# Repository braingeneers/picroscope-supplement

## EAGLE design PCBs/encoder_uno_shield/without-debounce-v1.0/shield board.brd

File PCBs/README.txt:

Power distribution board -> V8
Relay hub -> V3R1 -> JLCPCB
Below light -> V6 -> JLCPCB
Overhead light -> R5 -> PCBWAY

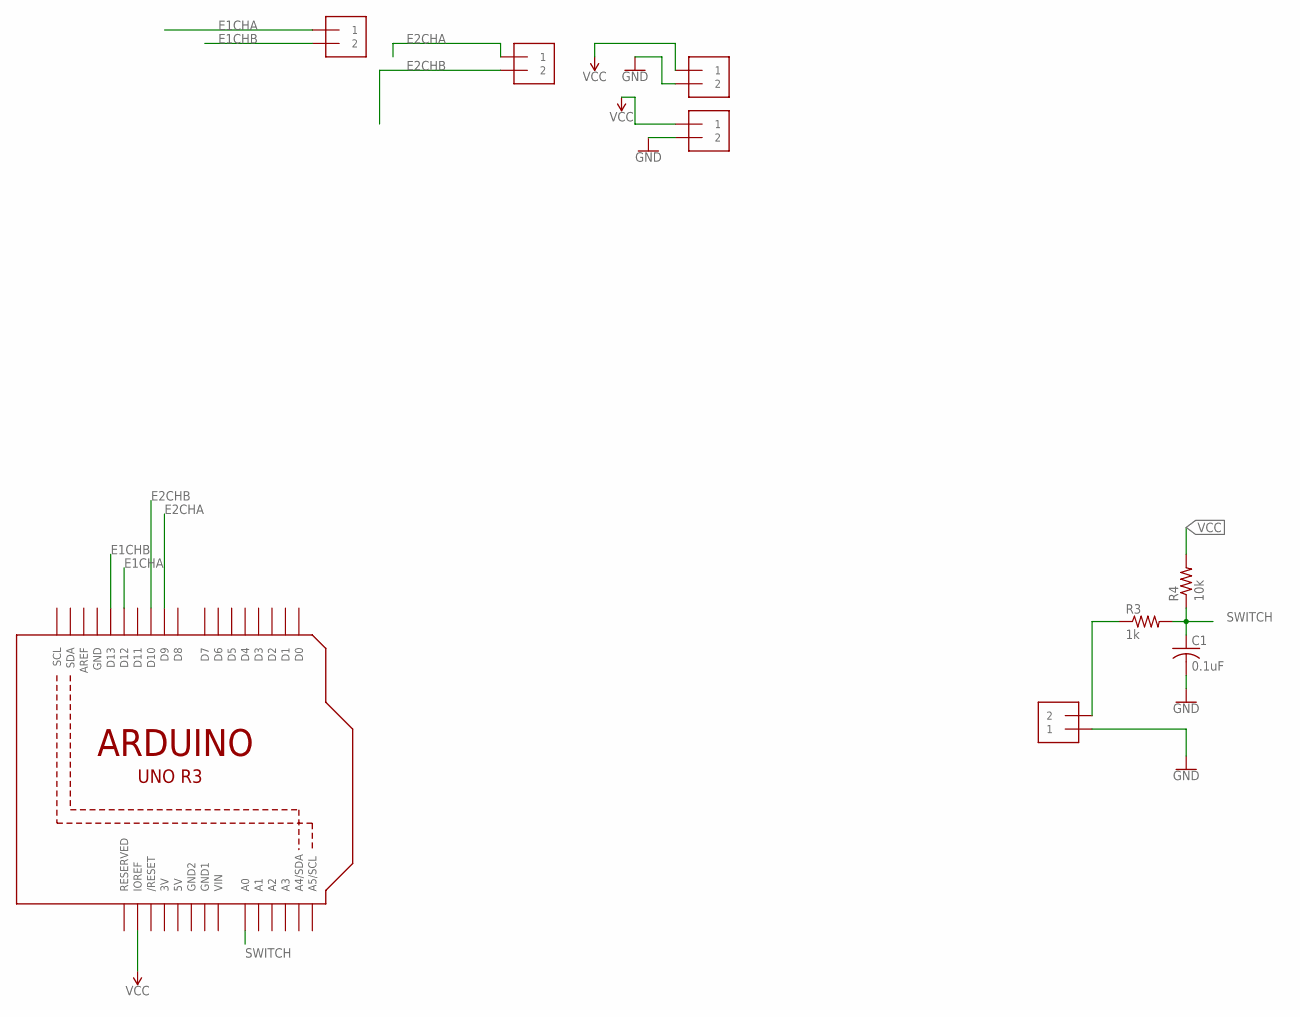
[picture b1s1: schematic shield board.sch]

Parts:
C1: 0.1uF; C0603
R3: 1k; R0603
R4: 10k; R0603
U1: ARDUINOR3-BPLACE
U$2, U$3, U$4, U$5, U$6: MOLEX_0039301022; MINI-FIT_JR_CONN

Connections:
3V: U1.3V
E1CHA: U1.D12, U$5.P$2 (1)
E1CHB: U1.D13, U$5.P$1 (2)
E2CHA: U1.D9, U$6.P$2 (1)
E2CHB: U1.D10, U$6.P$1 (2)
GND: C1.2, U1.GND, U$2.P$2 (1), U$3.P$1 (2), U$4.P$1 (2)
GND1: U1.GND1
GND2: U1.GND2
unnamed: R3.1, U$2.P$1 (2)
SWITCH: C1.1, R3.2, R4.1, U1.A0
VCC: R4.2, U1.5V, U1.IOREF, U$3.P$2 (1), U$4.P$2 (1)
VIN: U1.VIN

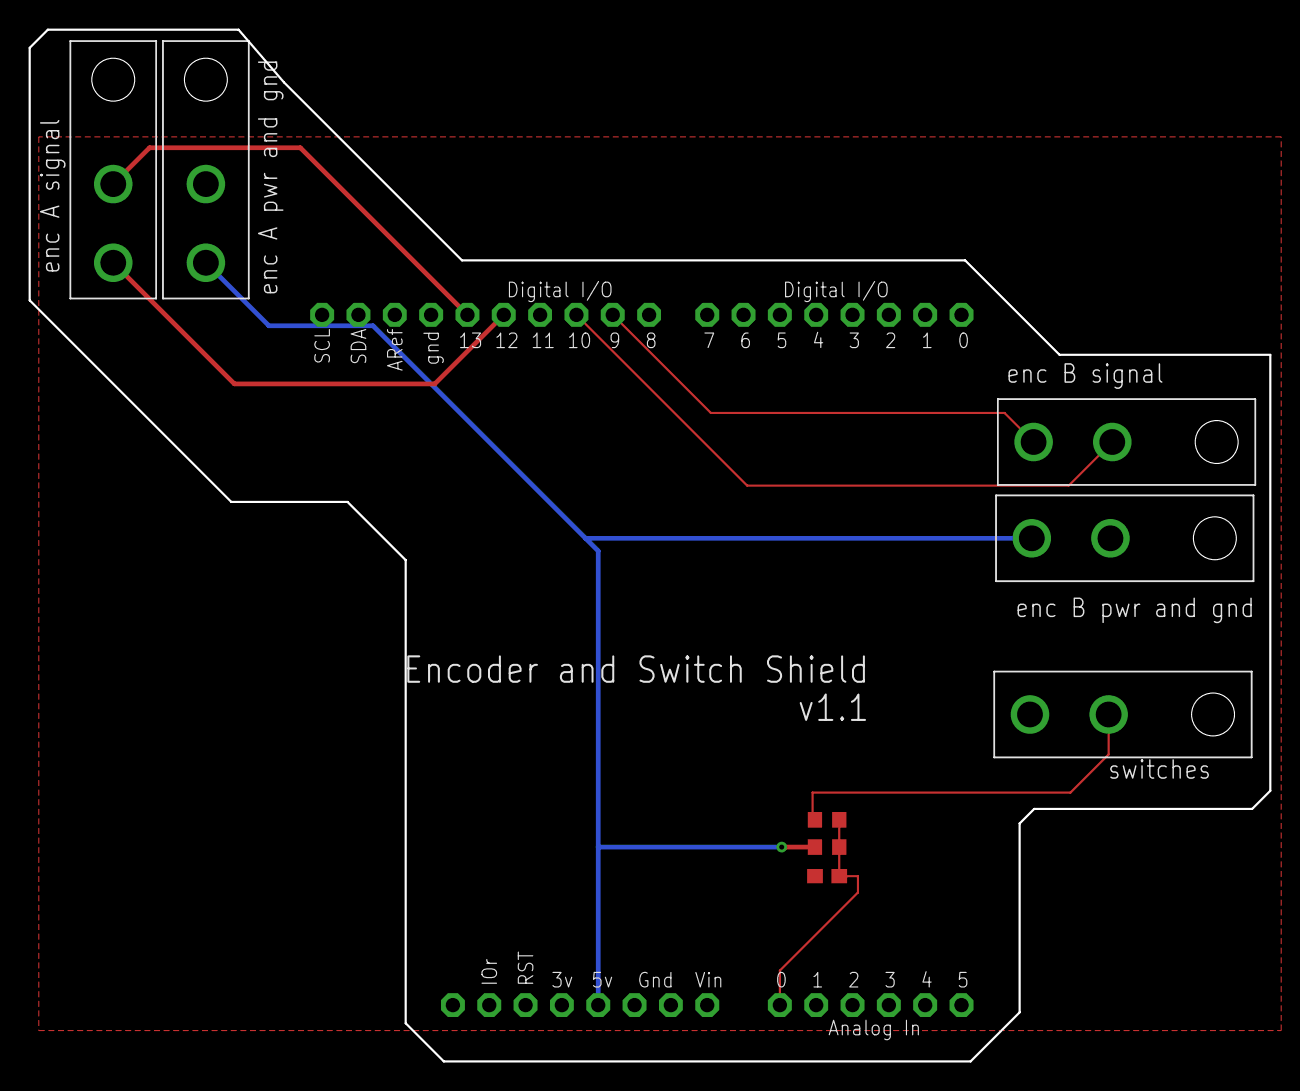
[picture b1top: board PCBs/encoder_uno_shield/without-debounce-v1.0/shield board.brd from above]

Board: 2 copper layers, 86.7 x 72.1 mm, 9 parts (0 on the bottom side), 8 nets.

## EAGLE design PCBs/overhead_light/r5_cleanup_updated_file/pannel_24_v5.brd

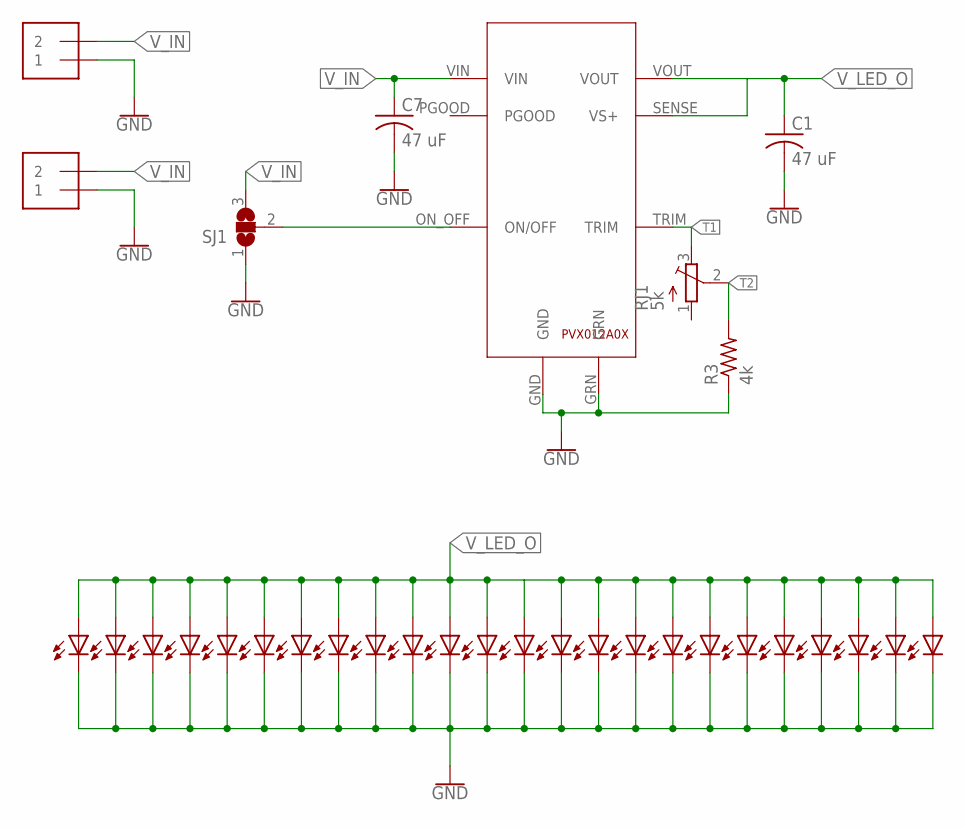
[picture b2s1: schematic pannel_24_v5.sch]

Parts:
C1, C7: 47 uF; C1210
R3: 4k; R0603
RJ1: 5k; 3223W
SJ1: SJ2W; SJ_2
U$1, U$2, U$3, U$4, U$5, U$6, U$7, U$8, U$9, U$10, U$11, U$12, U$13, U$14, U$15, U$16, U$17, U$18, U$19, U$20, U$21, U$22, U$23, U$24: LED; 3WLED
U$25: PVX012A0XV1; PVX012A0X
U$26, U$27: MOLEX_0039301022; MINI-FIT_JR_CONN

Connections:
GND: C1.2, C7.2, R3.1, SJ1.1, U$1.P$2 (C), U$2.P$2 (C), U$3.P$2 (C), U$4.P$2 (C), U$5.P$2 (C), U$6.P$2 (C), U$7.P$2 (C), U$8.P$2 (C), U$9.P$2 (C), U$10.P$2 (C), U$11.P$2 (C), U$12.P$2 (C), U$13.P$2 (C), U$14.P$2 (C), U$15.P$2 (C), U$16.P$2 (C), U$17.P$2 (C), U$18.P$2 (C), U$19.P$2 (C), U$20.P$2 (C), U$21.P$2 (C), U$22.P$2 (C), U$23.P$2 (C), U$24.P$2 (C), U$25.GND, U$25.GRN, U$26.P$2 (1), U$27.P$2 (1)
ON_OFF: SJ1.2, U$25.ON_OFF (ON/OFF)
T1: RJ1.3 (E), U$25.TRIM
T2: R3.2, RJ1.2 (S)
V_IN: C7.1, SJ1.3, U$25.VIN, U$26.P$1 (2), U$27.P$1 (2)
V_LED_O: C1.1, U$1.P$1 (A), U$2.P$1 (A), U$3.P$1 (A), U$4.P$1 (A), U$5.P$1 (A), U$6.P$1 (A), U$7.P$1 (A), U$8.P$1 (A), U$9.P$1 (A), U$10.P$1 (A), U$11.P$1 (A), U$12.P$1 (A), U$13.P$1 (A), U$14.P$1 (A), U$15.P$1 (A), U$16.P$1 (A), U$17.P$1 (A), U$18.P$1 (A), U$19.P$1 (A), U$20.P$1 (A), U$21.P$1 (A), U$22.P$1 (A), U$23.P$1 (A), U$24.P$1 (A), U$25.SENSE (VS+), U$25.VOUT

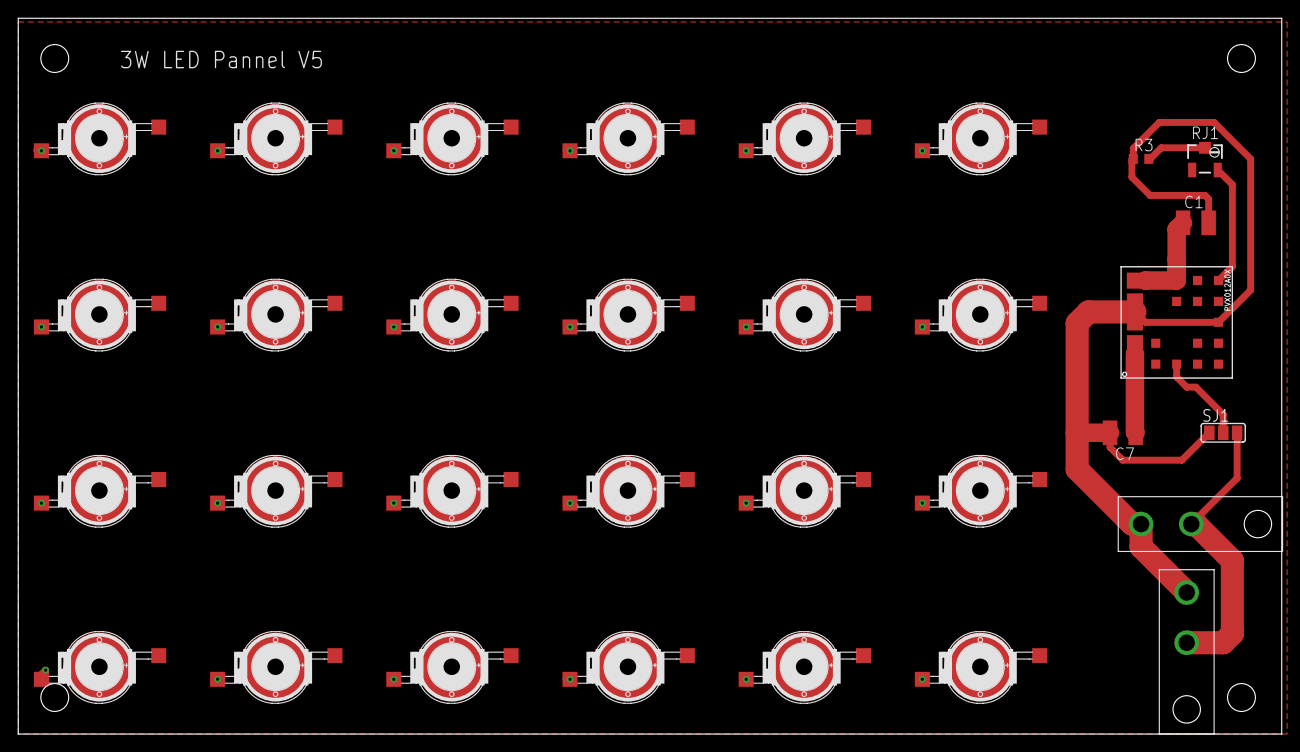
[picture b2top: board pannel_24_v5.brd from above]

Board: 2 copper layers, 138.4 x 78.4 mm, 32 parts (0 on the bottom side), 6 nets.

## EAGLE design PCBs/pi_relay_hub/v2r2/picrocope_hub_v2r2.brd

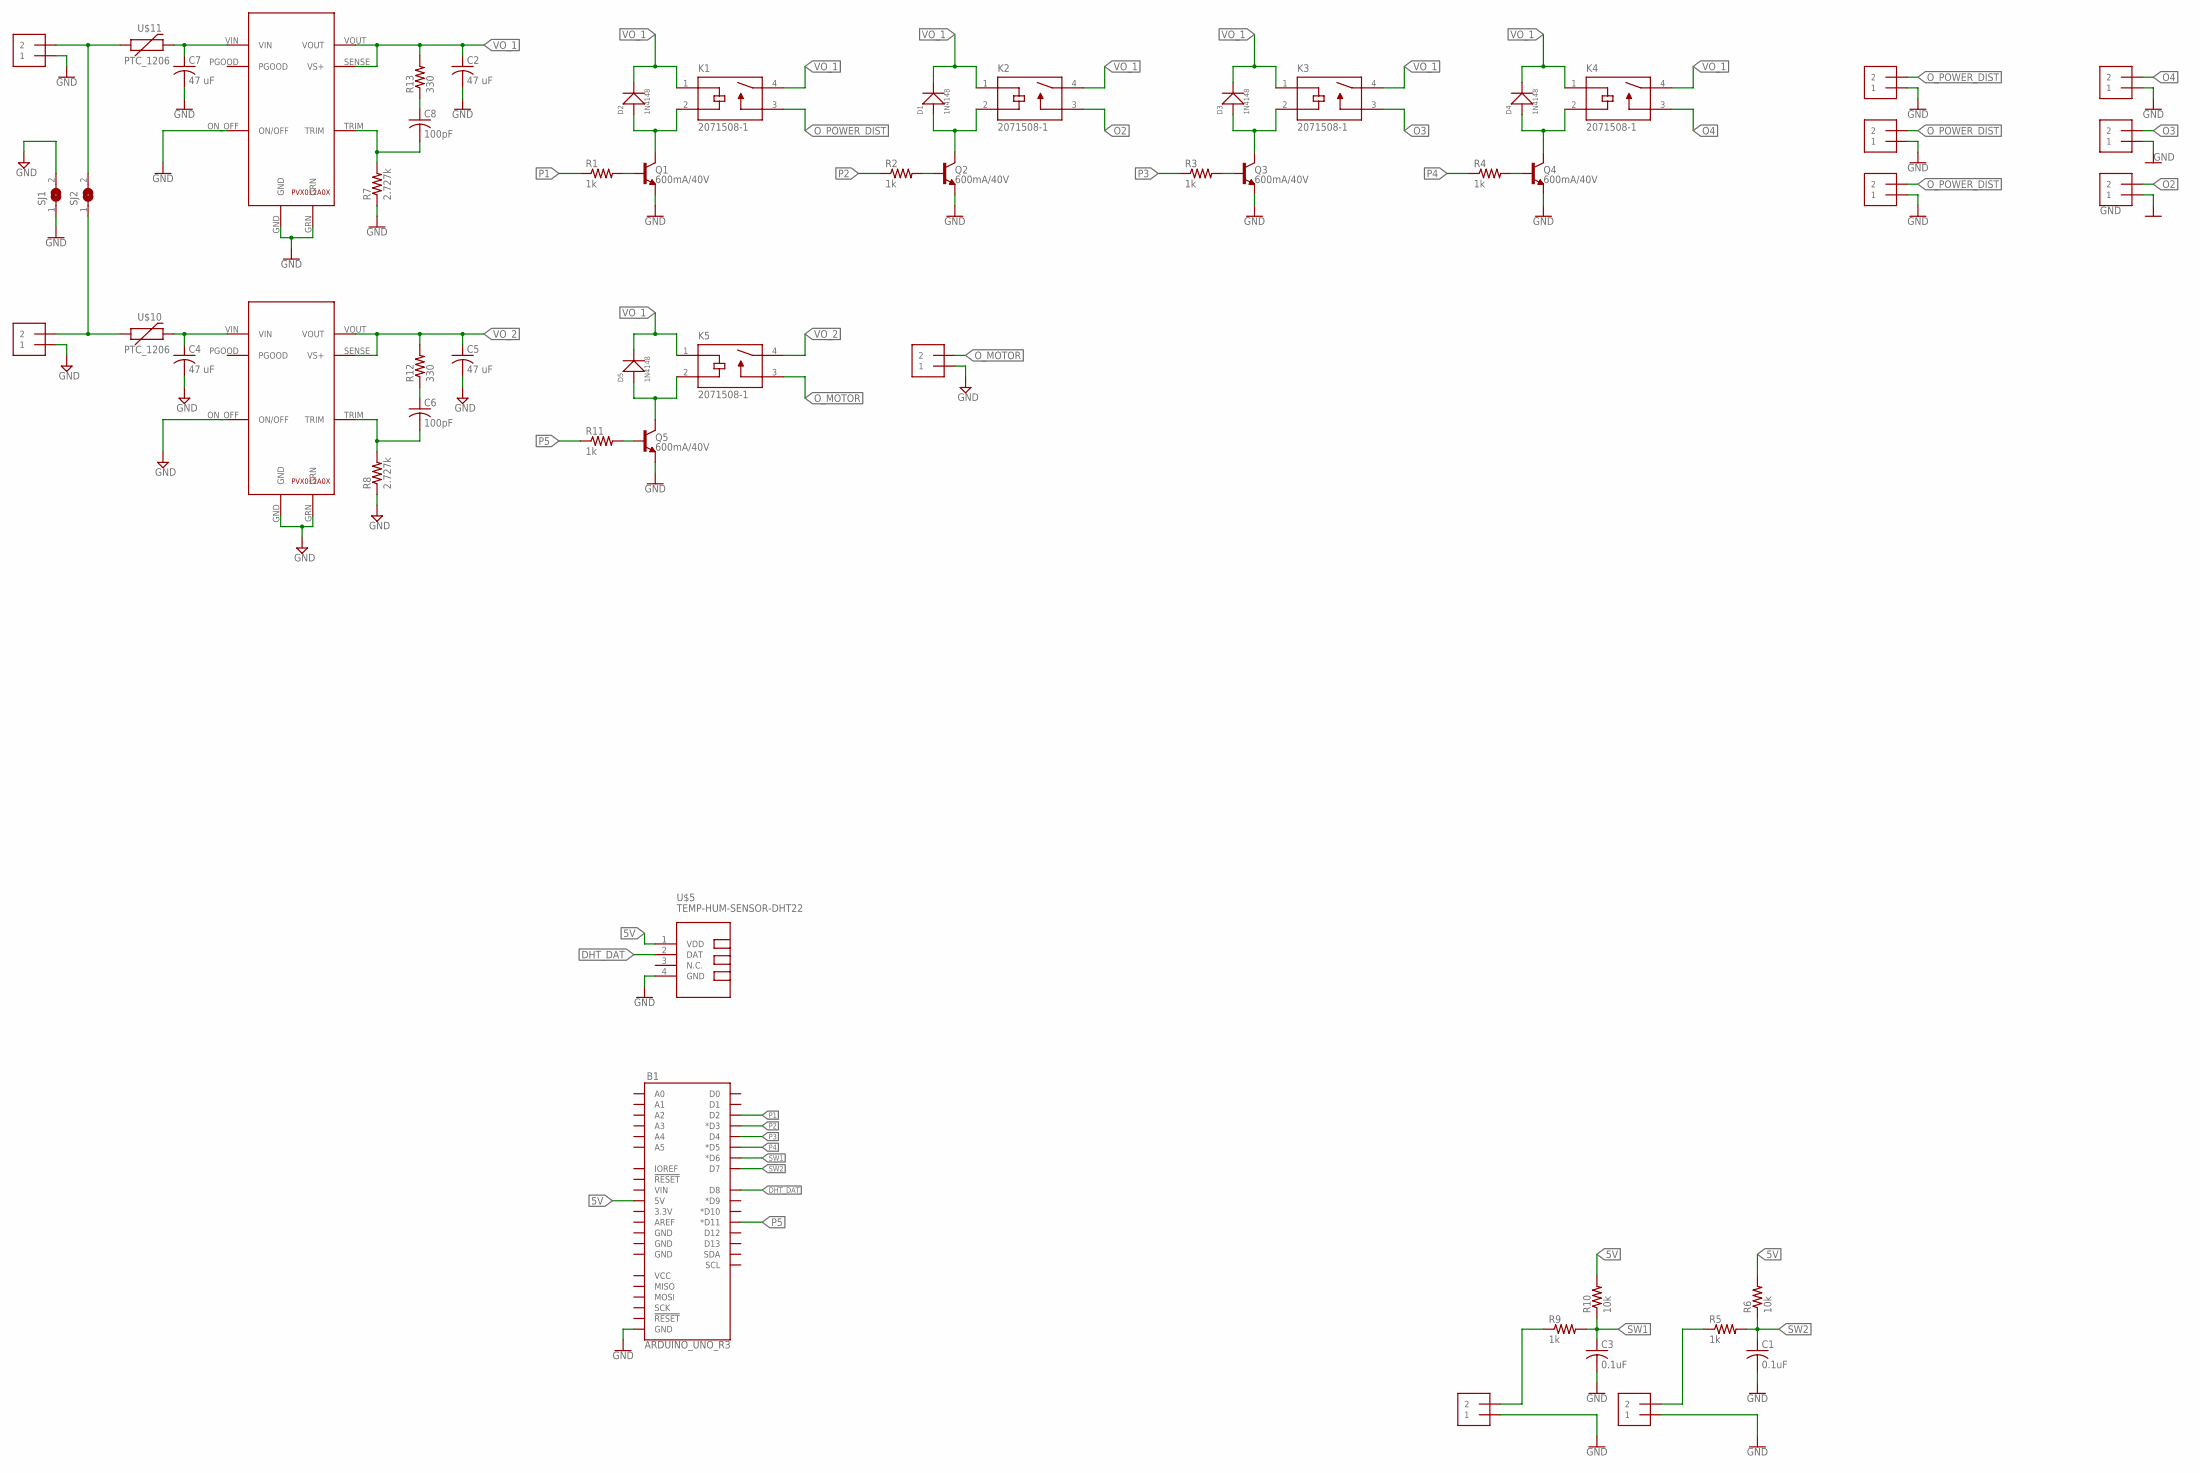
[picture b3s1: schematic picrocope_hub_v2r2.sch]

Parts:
B1: ARDUINO_UNO_R3; ARDUINO_R3
C1, C3: 0.1uF; C0603
C2, C4, C5, C7: 47 uF; C1210
C6, C8: 100pF; C0603
D1, D2, D3, D4, D5: 1N4148; LL-34
K1, K2, K3, K4, K5: 2071508-1; RELAY_2071508-1
Q1, Q2, Q3, Q4, Q5: 600mA/40V; SOT23-3
R1, R2, R3, R4, R5, R9, R11: 1k; R0603
R6, R10: 10k; R0603
R7, R8: 2.727k; R0603
R12, R13: 330; R0603
SJ1, SJ2: SJ
U$1, U$2: PVX012A0XV1; PVX012A0X
U$3, U$4, U$6, U$7, U$8, U$9, U$12, U$13, U$14: MOLEX_0039301022; MINI-FIT_JR_CONN
U$5: TEMP-HUM-SENSOR-DHT22
U$10, U$11: PTC_1206; 1206
U$15, U$16: MOLEX_0039296028; MINI-FIT_JR_VERTICAL_CONN

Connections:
5V: B1.5V, R6.2, R10.2, U$5.1 (VDD)
DHT_DAT: B1.D8, U$5.2 (DAT)
GND: B1.GND@1 (GND), C1.2, C2.2, C3.2, C7.2, Q1.2 (E), Q2.2 (E), Q3.2 (E), Q4.2 (E), Q5.2 (E), R7.1, SJ1.1, U$1.GND, U$1.GRN, U$1.ON_OFF (ON/OFF), U$3.P$2 (1), U$5.4 (GND), U$6.P$2 (1), U$7.P$2 (1), U$8.P$2 (1), U$9.P$2 (1), U$12.P$2 (1), U$13.P$2 (1), U$15.P$1 (1), U$16.P$1 (1)
GND2: C4.2, C5.2, R8.1, SJ1.2, U$2.GND, U$2.GRN, U$2.ON_OFF (ON/OFF), U$4.P$2 (1), U$14.P$2 (1)
unnamed: Q1.1 (B), R1.2
unnamed: D2.A (+), K1.2 (COIL2), Q1.3 (C)
unnamed: SJ2.1, U$4.P$1 (2), U$10.1
unnamed: R5.1, U$16.P$2 (2)
unnamed: Q2.1 (B), R2.2
unnamed: D1.A (+), K2.2 (COIL2), Q2.3 (C)
unnamed: Q3.1 (B), R3.2
unnamed: D3.A (+), K3.2 (COIL2), Q3.3 (C)
unnamed: Q4.1 (B), R4.2
unnamed: D4.A (+), K4.2 (COIL2), Q4.3 (C)
unnamed: R9.1, U$15.P$2 (2)
unnamed: Q5.1 (B), R11.2
unnamed: C6.1, R12.1
unnamed: C8.1, R13.1
unnamed: D5.A (+), K5.2 (COIL2), Q5.3 (C)
unnamed: C6.2, R8.2, U$2.TRIM
unnamed: C8.2, R7.2, U$1.TRIM
unnamed: SJ2.2, U$3.P$1 (2), U$11.1
O2: K2.3 (NO), U$7.P$1 (2)
O3: K3.3 (NO), U$8.P$1 (2)
O4: K4.3 (NO), U$9.P$1 (2)
O_MOTOR: K5.3 (NO), U$14.P$1 (2)
O_POWER_DIST: K1.3 (NO), U$6.P$1 (2), U$12.P$1 (2), U$13.P$1 (2)
P1: B1.D2, R1.1
P2: B1.D3 (*D3), R2.1
P3: B1.D4, R3.1
P4: B1.D5 (*D5), R4.1
P5: B1.D11 (*D11), R11.1
SW1: B1.D6 (*D6), C3.1, R9.2, R10.1
SW2: B1.D7, C1.1, R5.2, R6.1
VIN_1: C7.1, U$1.VIN, U$11.2
VIN_2: C4.1, U$2.VIN, U$10.2
VO_1: C2.1, D1.C (-), D2.C (-), D3.C (-), D4.C (-), D5.C (-), K1.1 (COIL1), K1.4 (COM), K2.1 (COIL1), K2.4 (COM), K3.1 (COIL1), K3.4 (COM), K4.1 (COIL1), K4.4 (COM), K5.1 (COIL1), R13.2, U$1.SENSE (VS+), U$1.VOUT
VO_2: C5.1, K5.4 (COM), R12.2, U$2.SENSE (VS+), U$2.VOUT

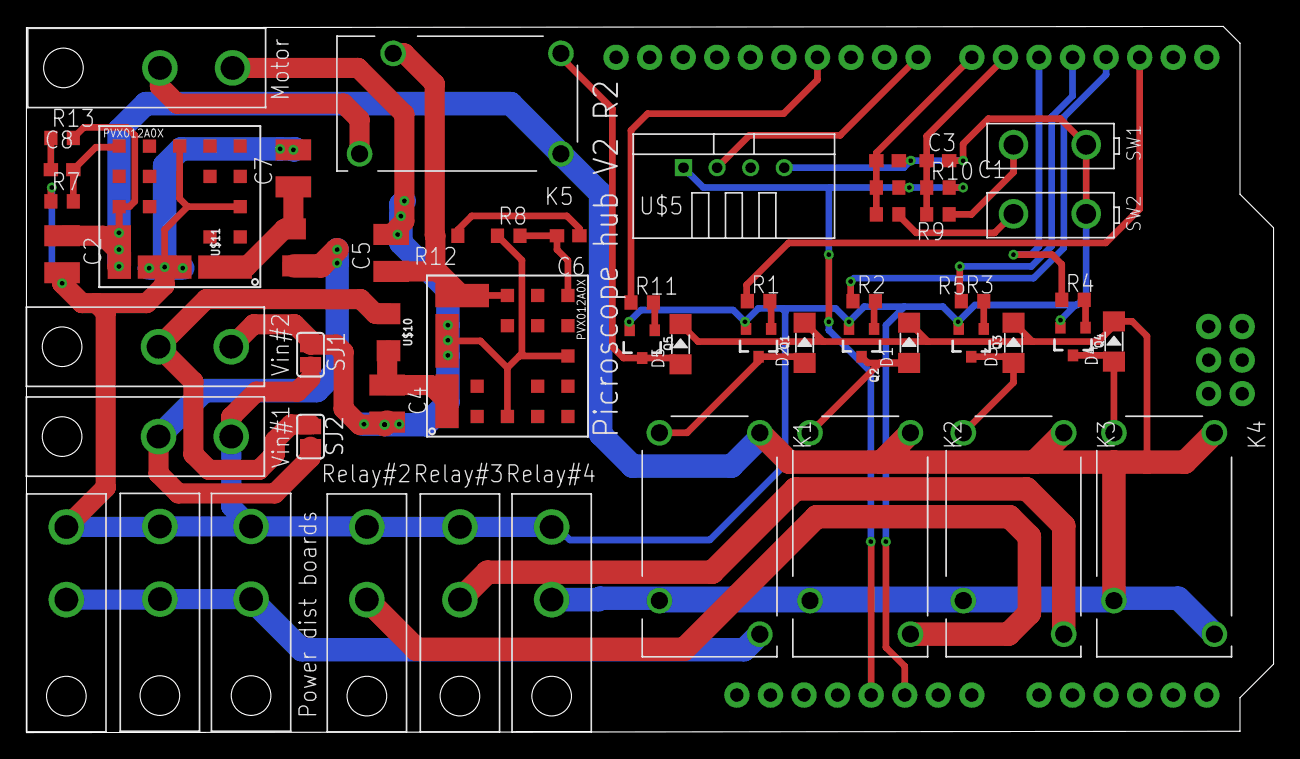
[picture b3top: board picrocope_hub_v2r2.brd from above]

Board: 2 copper layers, 94.4 x 53.4 mm, 55 parts (0 on the bottom side), 38 nets.

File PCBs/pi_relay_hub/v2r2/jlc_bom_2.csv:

Comment,Designator,Footprint,LCSC Part #(optional)
0.1uF,C1,C0603,C14663
47 uF,C2,C1210,C77101
0.1uF,C3,C0603,C14663
47 uF,C4,C1210,C77101
47 uF,C5,C1210,C77101
100pF,C6,C0603,C14858
47 uF,C7,C1210,C77101
100pF,C8,C0603,C14858
1N4148,D1,LL-34,C81598
1N4148,D2,LL-34,C81598
1N4148,D3,LL-34,C81598
1N4148,D4,LL-34,C81598
1N4148,D5,LL-34,C81598
600mA/40V,Q1,SOT23-3,C8512
600mA/40V,Q2,SOT23-3,C8512
600mA/40V,Q3,SOT23-3,C8512
600mA/40V,Q4,SOT23-3,C8512
600mA/40V,Q5,SOT23-3,C8512
1k,R1,R0603,C21190
1k,R2,R0603,C21190
1k,R3,R0603,C21190
1k,R4,R0603,C21190
1k,R5,R0603,C21190
10k,R6,R0603,C25804
2.727k,R7,R0603,C13167
2.727k,R8,R0603,C13167
1k,R9,R0603,C21190
10k,R10,R0603,C25804
1k,R11,R0603,C21190
330,R12,R0603,C23138
330,R13,R0603,C23138

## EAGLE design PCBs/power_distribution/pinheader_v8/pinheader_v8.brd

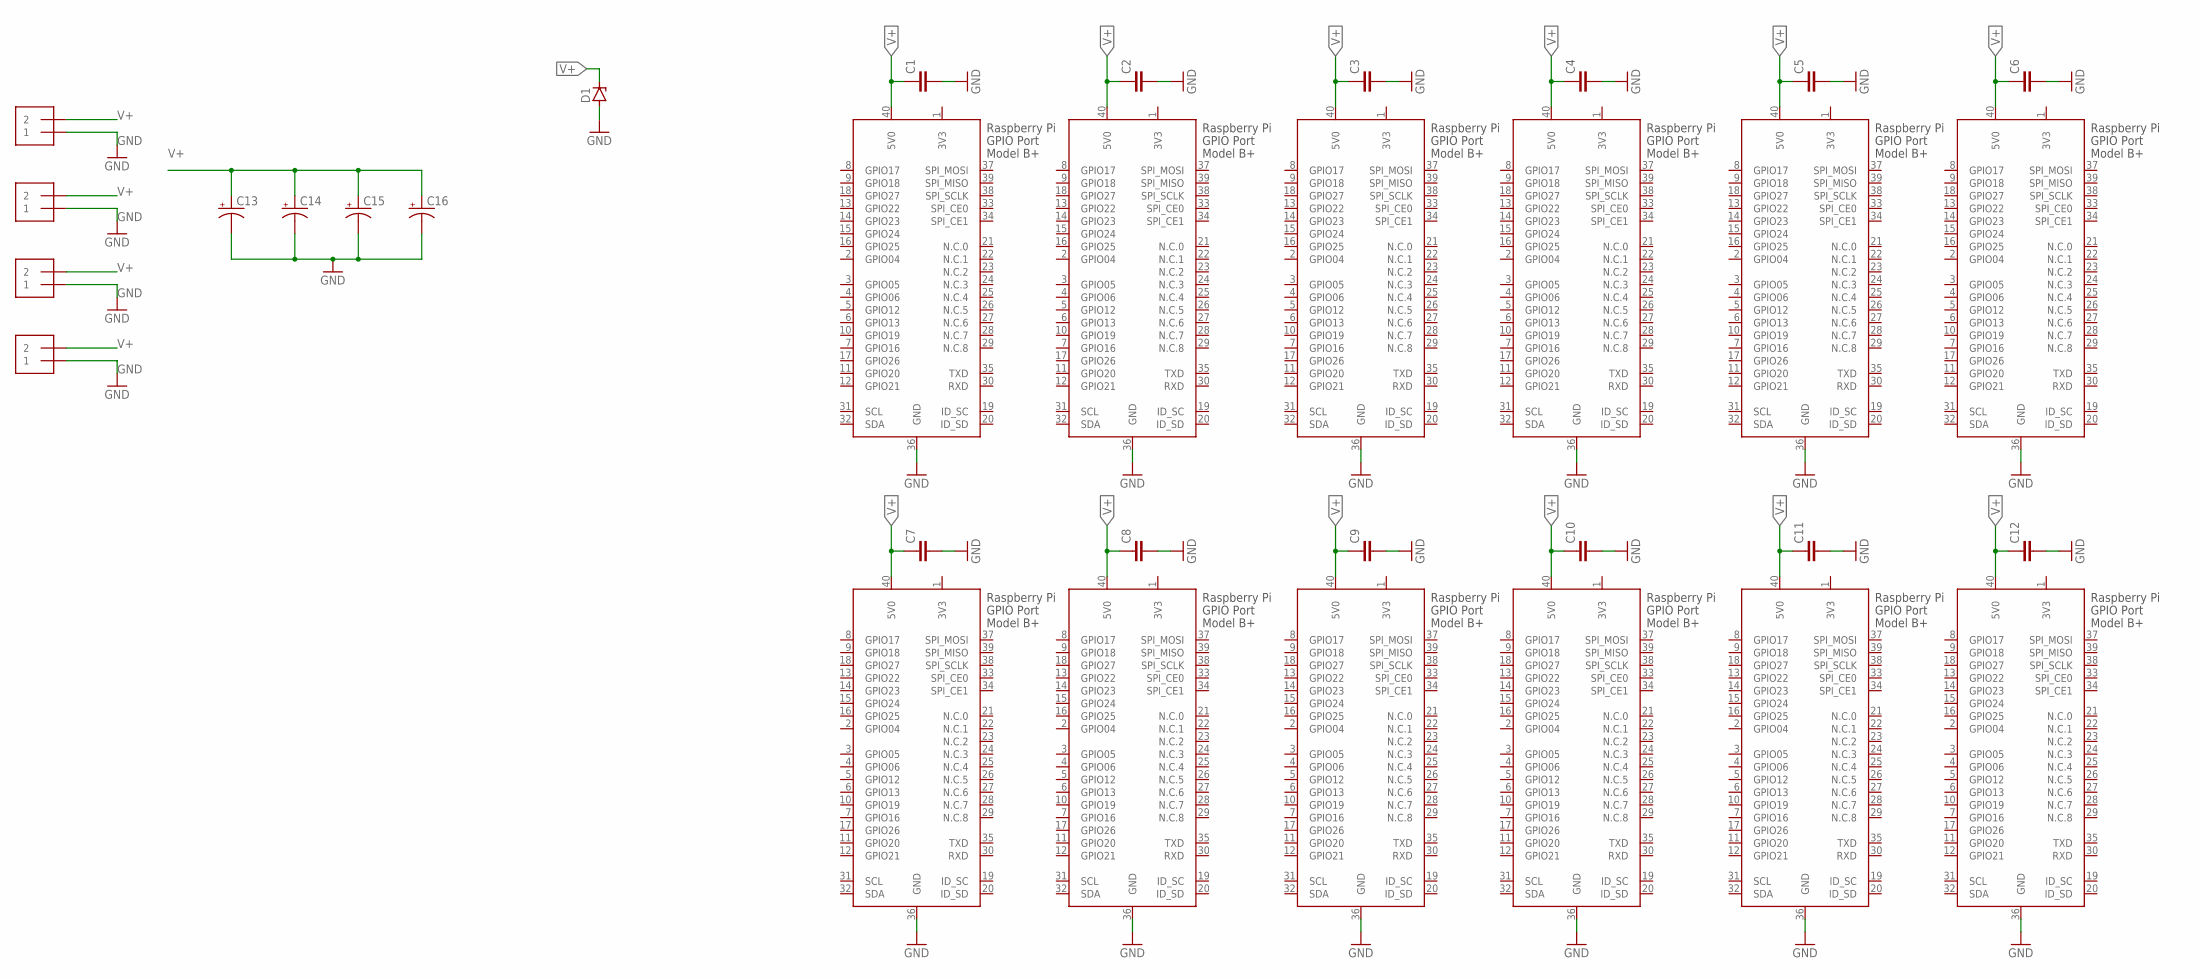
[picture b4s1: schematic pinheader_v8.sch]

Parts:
C1, C2, C3, C4, C5, C6, C7, C8, C9, C10, C11, C12: C-EUC0603; C0603
C13, C14, C15, C16: CPOL-USE3.5-8; E3,5-8
D1: ZENER-DIODESOT223; SOT223
U$1, U$2, U$3, U$4, U$5, U$6, U$7, U$8, U$9, U$10, U$11, U$12: RASPI_GPIO_B+_PWR; RASPI_GPIO_B+_PIN
U$13, U$14, U$15, U$16: MOLEX_0039301022; MINI-FIT_JR_CONN

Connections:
3V3: U$1.1 (3V3), U$2.1 (3V3), U$3.1 (3V3), U$4.1 (3V3), U$5.1 (3V3), U$6.1 (3V3), U$7.1 (3V3), U$8.1 (3V3), U$9.1 (3V3), U$10.1 (3V3), U$11.1 (3V3), U$12.1 (3V3)
GND: C1.2, C2.2, C3.2, C4.2, C5.2, C6.2, C7.2, C8.2, C9.2, C10.2, C11.2, C12.2, C13.-, C14.-, C15.-, C16.-, D1.1 (A), U$1.36 (GND), U$2.36 (GND), U$3.36 (GND), U$4.36 (GND), U$5.36 (GND), U$6.36 (GND), U$7.36 (GND), U$8.36 (GND), U$9.36 (GND), U$10.36 (GND), U$11.36 (GND), U$12.36 (GND), U$13.P$2 (1), U$14.P$2 (1), U$15.P$2 (1), U$16.P$2 (1)
V+: C1.1, C2.1, C3.1, C4.1, C5.1, C6.1, C7.1, C8.1, C9.1, C10.1, C11.1, C12.1, C13.+, C14.+, C15.+, C16.+, D1.4 (C), U$1.40 (5V0), U$2.40 (5V0), U$3.40 (5V0), U$4.40 (5V0), U$5.40 (5V0), U$6.40 (5V0), U$7.40 (5V0), U$8.40 (5V0), U$9.40 (5V0), U$10.40 (5V0), U$11.40 (5V0), U$12.40 (5V0), U$13.P$1 (2), U$14.P$1 (2), U$15.P$1 (2), U$16.P$1 (2)

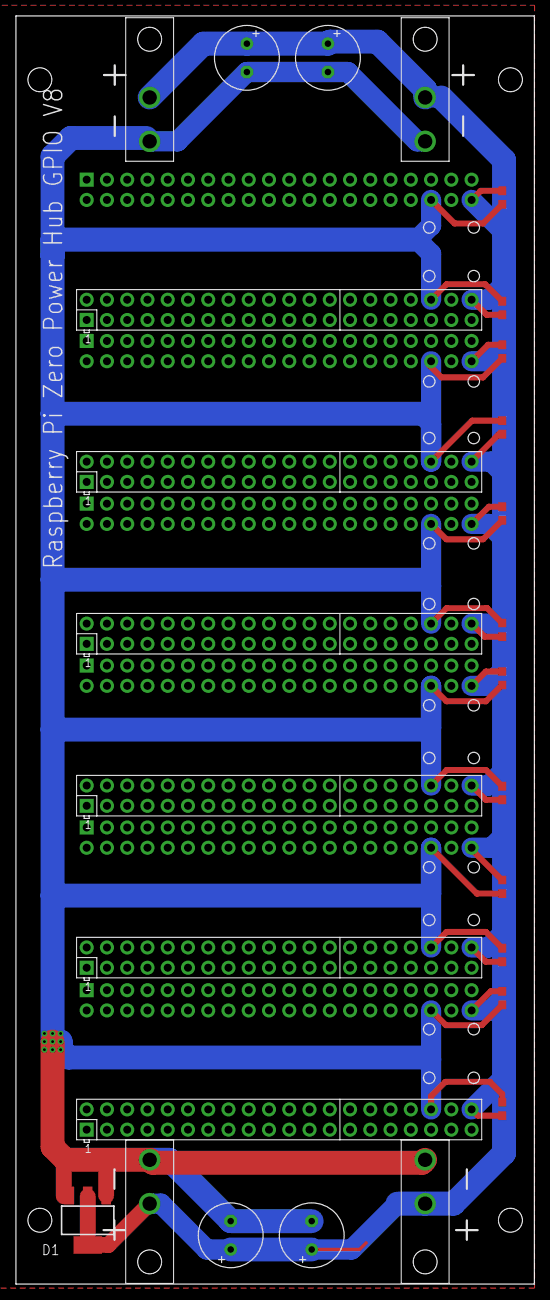
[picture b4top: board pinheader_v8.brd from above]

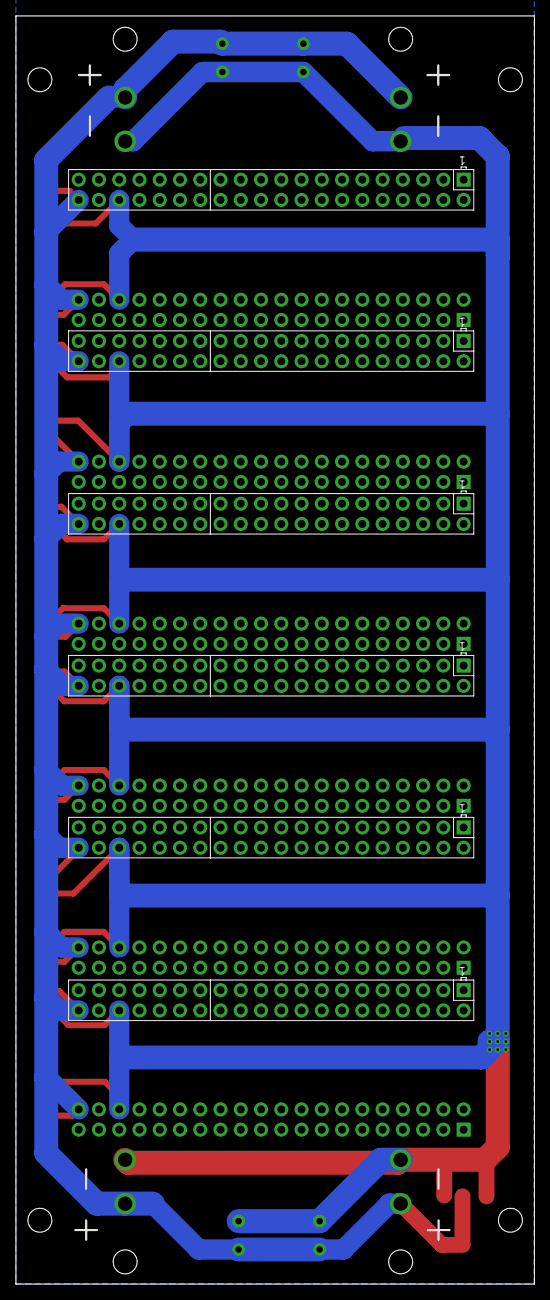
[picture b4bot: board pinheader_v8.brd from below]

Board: 2 copper layers, 65.0 x 159.0 mm, 33 parts (6 on the bottom side), 3 nets.

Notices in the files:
parts and their libraries:
SparkFun-PowerSymbols: Licensing: Creative Commons ShareAlike 4.0 International - https://creativecommons.org/licenses/by-sa/4.0
diy-modules: Released under the Creative Commons Attribution 4.0 International License: http://creativecommons.org/licenses/by/4.0
